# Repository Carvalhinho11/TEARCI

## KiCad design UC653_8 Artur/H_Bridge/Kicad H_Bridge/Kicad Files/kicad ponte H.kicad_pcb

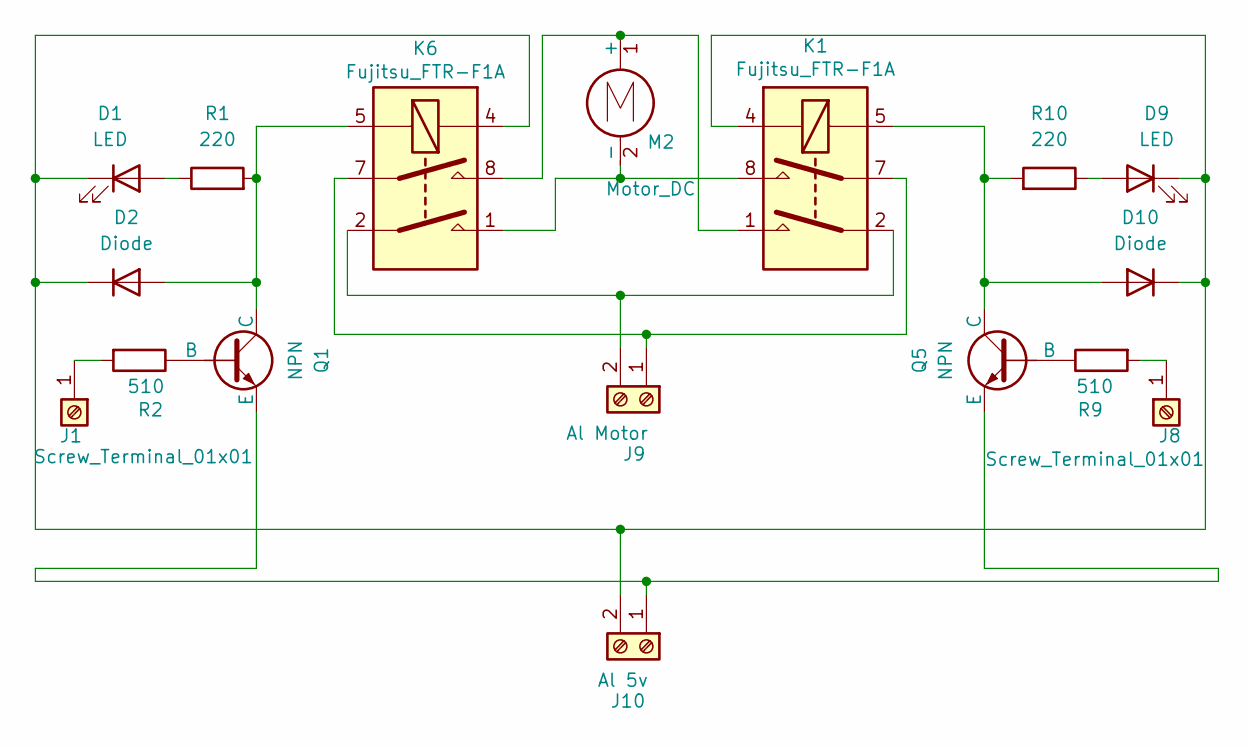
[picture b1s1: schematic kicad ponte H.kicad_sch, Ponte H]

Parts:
D1, D9: LED; LED_D3.0mm
D2, D10: Diode; D_SOD-523
J1, J8: Screw_Terminal_01x01; TerminalBlock_MetzConnect_360271_1x01_Horizontal_ScrewM3.0_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
J9: Al Motor; TerminalBlock_MetzConnect_Type101_RT01602HBWC_1x02_P5.08mm_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
J10: Al 5v; TerminalBlock_MetzConnect_Type101_RT01602HBWC_1x02_P5.08mm_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
K1, K6: Fujitsu_FTR-F1A; Relay_DPST_Fujitsu_FTR-F1A
M2: Motor_DC; TerminalBlock_MetzConnect_Type011_RT05502HBLC_1x02_P5.00mm_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
Q1, Q5: NPN; TO-92
R1, R10: 220; R_Axial_DIN0207_L6.3mm_D2.5mm_P7.62mm_Horizontal
R2, R9: 510; R_Axial_DIN0207_L6.3mm_D2.5mm_P7.62mm_Horizontal

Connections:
unnamed: D1.2 (A), R1.1
unnamed: D1.1 (K), D2.1 (K), D9.1 (K), D10.1 (K), J10.2, K1.4, K6.4
unnamed: D2.2 (A), K6.5, Q1.1 (C), R1.2
unnamed: D9.2 (A), R10.1
unnamed: D10.2 (A), K1.5, Q5.1 (C), R10.2
unnamed: J1.1, R2.2
unnamed: J8.1, R9.2
unnamed: J9.1, K1.7, K6.7
unnamed: J9.2, K1.2, K6.2
unnamed: J10.1, Q1.3 (E), Q5.3 (E)
unnamed: K1.1, K6.8, M2.1 (+)
unnamed: K1.8, K6.1, M2.2 (-)
unnamed: Q1.2 (B), R2.1
unnamed: Q5.2 (B), R9.1

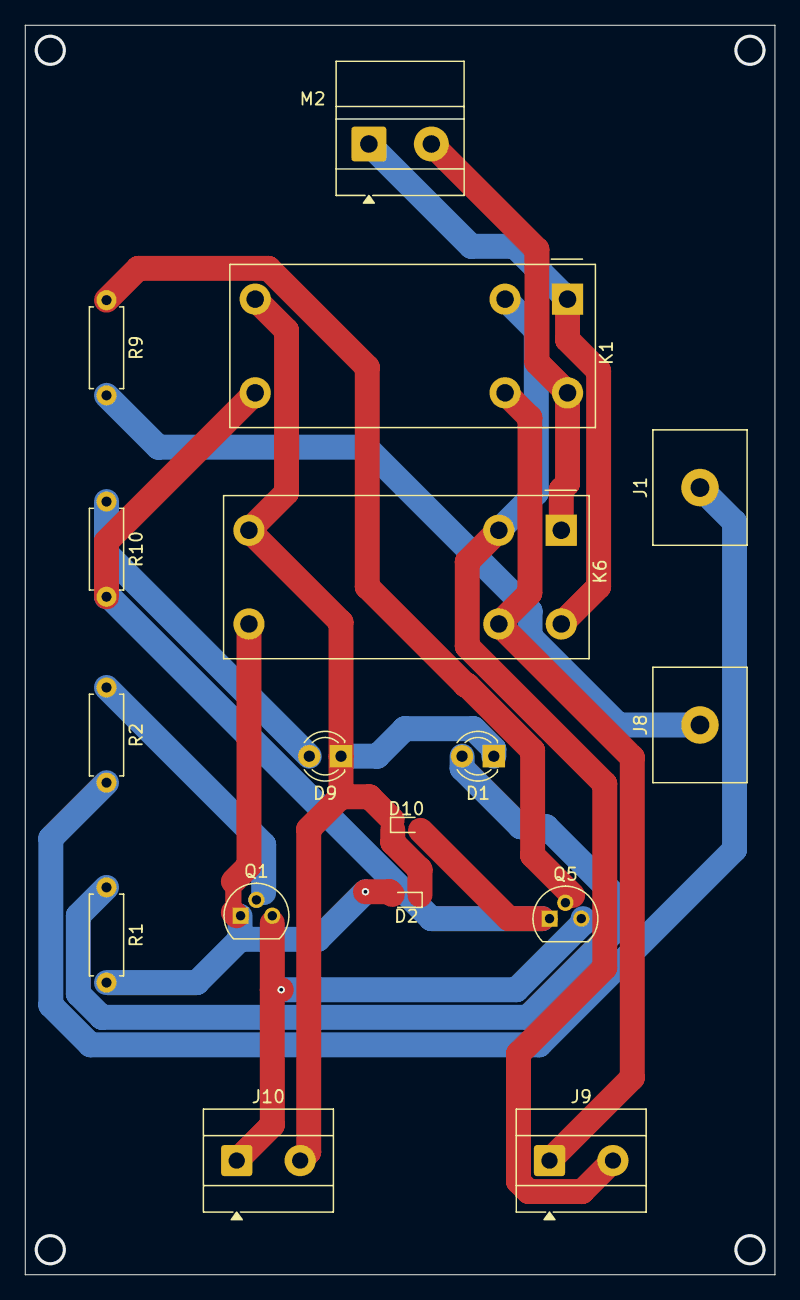
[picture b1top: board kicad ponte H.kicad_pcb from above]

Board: 2 copper layers, 60.0 x 100.0 mm, 17 parts (0 on the bottom side), 14 nets.

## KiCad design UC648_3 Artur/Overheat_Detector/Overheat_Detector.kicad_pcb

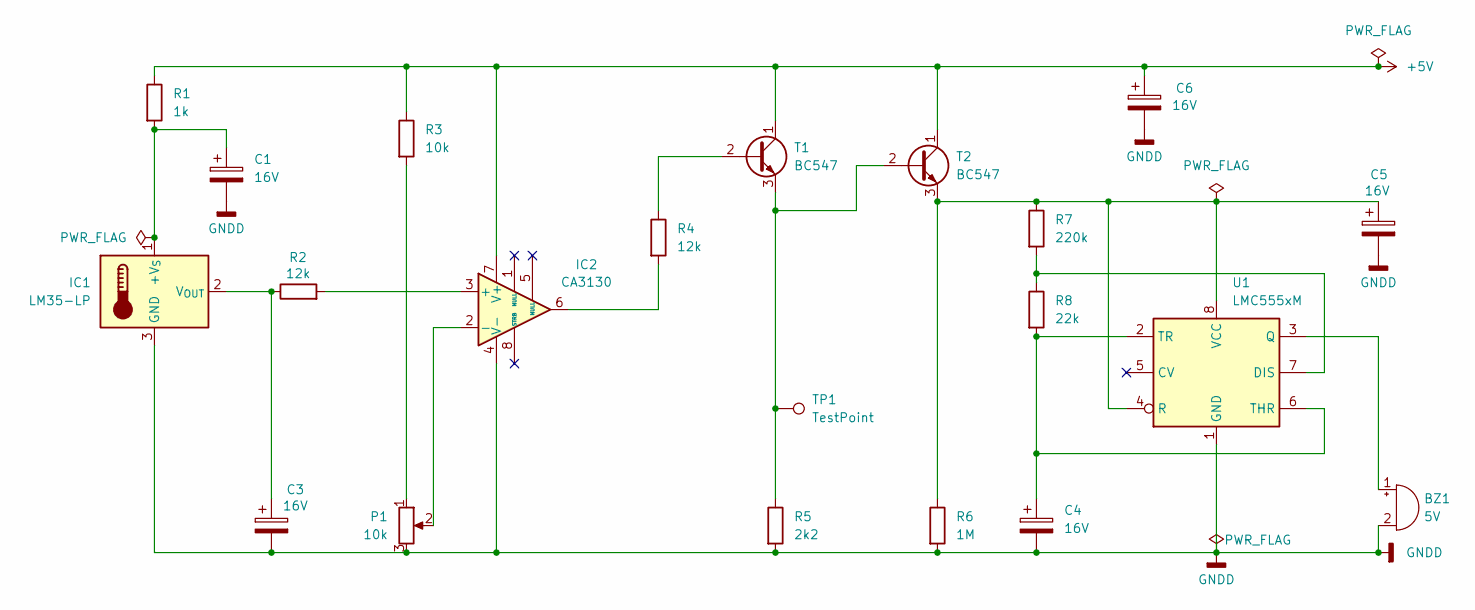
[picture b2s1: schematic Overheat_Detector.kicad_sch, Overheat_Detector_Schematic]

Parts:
BZ1: 5V; Buzzer_15x7.5RM7.6
C1, C3, C4, C5, C6: 16V; CP_Radial_D5.0mm_P2.00mm
IC1: LM35-LP; TO-92_Inline
IC2: CA3130; DIP-8_W7.62mm_LongPads
P1: 10k; Potentiometer_Bourns_3299W_Vertical
R1: 1k; R_Axial_DIN0204_L3.6mm_D1.6mm_P5.08mm_Horizontal
R2, R4: 12k; R_Axial_DIN0204_L3.6mm_D1.6mm_P5.08mm_Horizontal
R3: 10k; R_Axial_DIN0204_L3.6mm_D1.6mm_P5.08mm_Horizontal
R5: 2k2; R_Axial_DIN0204_L3.6mm_D1.6mm_P5.08mm_Horizontal
R6: 1M; R_Axial_DIN0204_L3.6mm_D1.6mm_P5.08mm_Horizontal
R7: 220k; R_Axial_DIN0204_L3.6mm_D1.6mm_P5.08mm_Horizontal
R8: 22k; R_Axial_DIN0204_L3.6mm_D1.6mm_P5.08mm_Horizontal
T1, T2: BC547; TO-92_Inline
TP1: TestPoint; TestPoint_THTPad_2.0x2.0mm_Drill1.0mm
U1: LMC555xM; SOIC-8_3.9x4.9mm_P1.27mm

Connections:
+5V: C6.1, IC2.7 (V+), R1.1, R3.1, T1.1 (C), T2.1 (C)
GNDD: BZ1.2 (-), C1.2, C3.2, C4.2, C5.2, C6.2, IC1.3 (GND), IC2.4 (V-), P1.3, R5.2, R6.2, U1.1 (GND)
unnamed: BZ1.1 (+), U1.3 (Q)
unnamed: C1.1, IC1.1 (+V_{S}), R1.2
unnamed: C3.1, IC1.2 (V_{OUT}), R2.1
unnamed: IC2.3 (+), R2.2
unnamed: IC2.2 (-), P1.2
unnamed: IC2.6, R4.2
unnamed: P1.1, R3.2
unnamed: R4.1, T1.2 (B)
unnamed: R5.1, T1.3 (E), T2.2 (B), TP1.1
unnamed: C5.1, R6.1, R7.1, T2.3 (E), U1.4 (R), U1.8 (VCC)
unnamed: R7.2, R8.1, U1.7 (DIS)
unnamed: C4.1, R8.2, U1.2 (TR), U1.6 (THR)

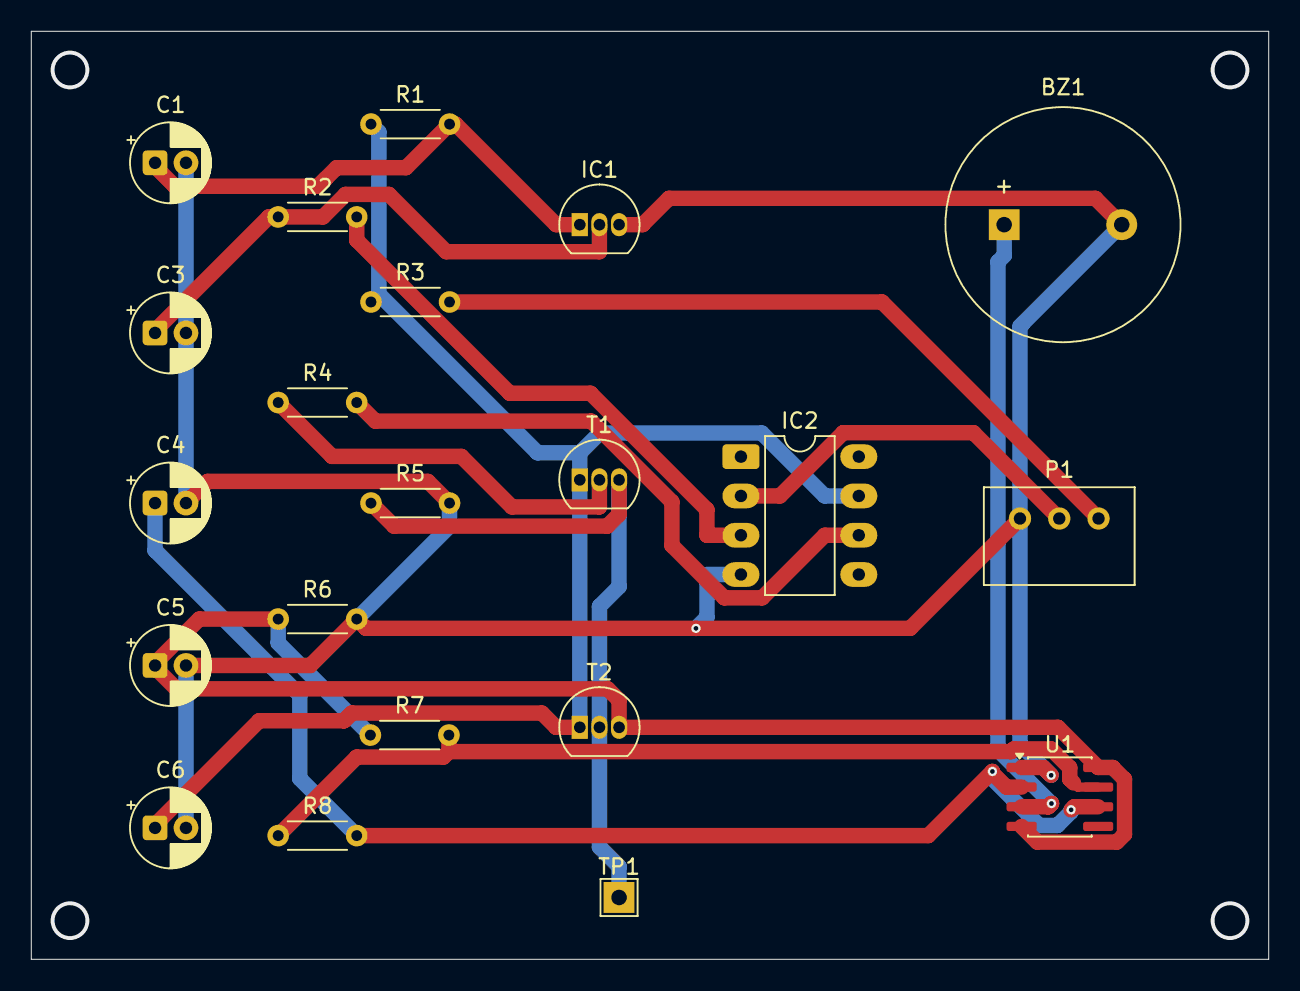
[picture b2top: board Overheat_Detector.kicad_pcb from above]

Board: 2 copper layers, 80.0 x 60.0 mm, 21 parts (0 on the bottom side), 14 nets.

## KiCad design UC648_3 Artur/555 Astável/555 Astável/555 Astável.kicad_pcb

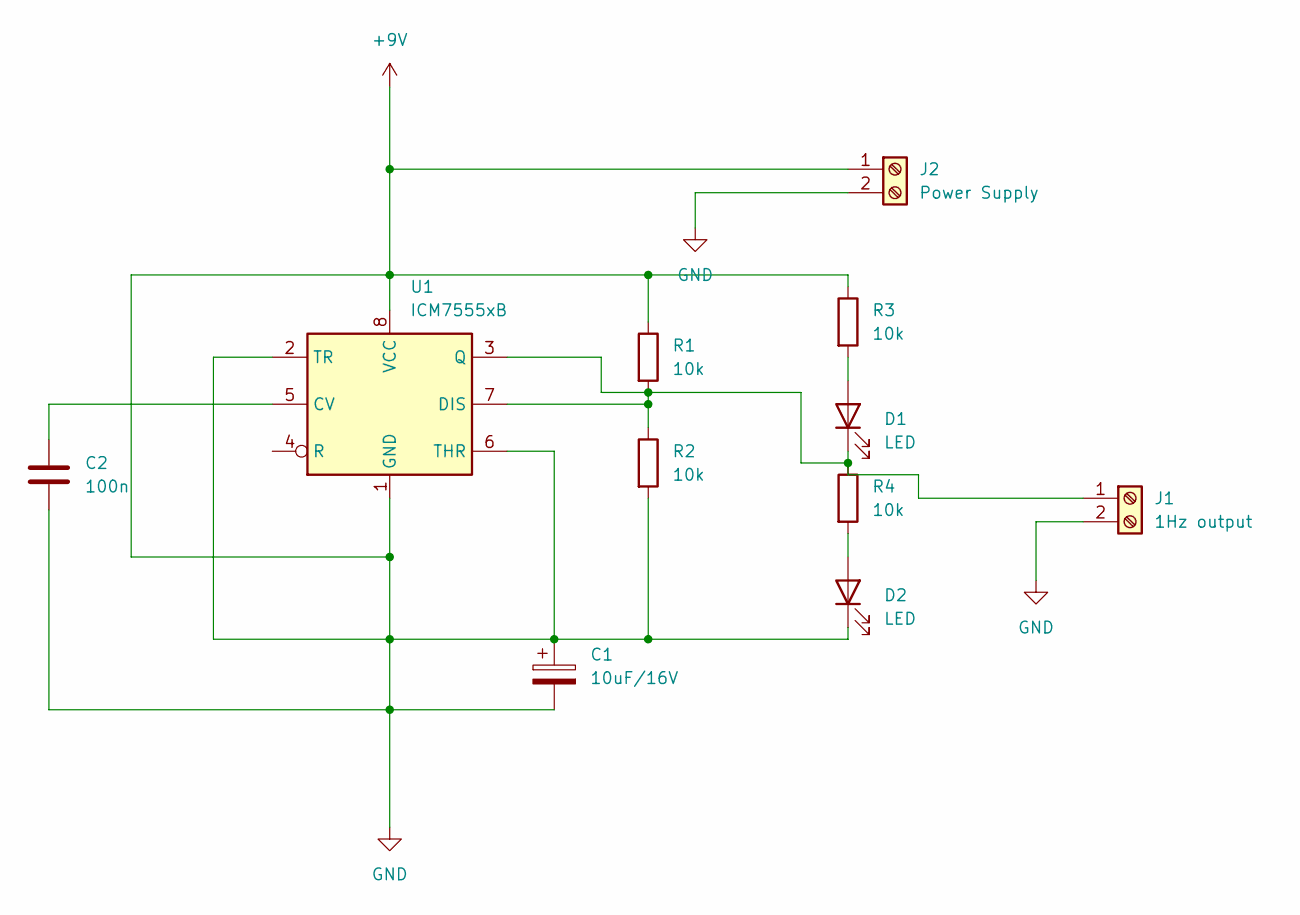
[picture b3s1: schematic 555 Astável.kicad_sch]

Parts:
C1: 10uF/16V; CP_Radial_D8.0mm_P5.00mm
C2: 100n; C_Rect_L18.0mm_W5.0mm_P15.00mm_FKS3_FKP3
D1, D2: LED; LED_D3.0mm
J1: 1Hz output; TerminalBlock_MaiXu_MX126-5.0-02P_1x02_P5.00mm
J2: Power Supply; TerminalBlock_MaiXu_MX126-5.0-02P_1x02_P5.00mm
R1, R2, R3, R4: 10k; R_Axial_DIN0204_L3.6mm_D1.6mm_P5.08mm_Horizontal
U1: ICM7555xB; DIP-8_W7.62mm

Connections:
+9V: C1.1, C1.2, C2.2, D2.1 (K), J1.2, J2.1, J2.2, R1.1, R2.2, R3.1, U1.1 (GND), U1.2 (TR), U1.6 (THR), U1.8 (VCC)
unnamed: D1.2 (A), R3.2
unnamed: D1.1 (K), J1.1, R1.2, R2.1, R4.1, U1.3 (Q), U1.7 (DIS)
unnamed: D2.2 (A), R4.2
unnamed: C2.1, U1.5 (CV)

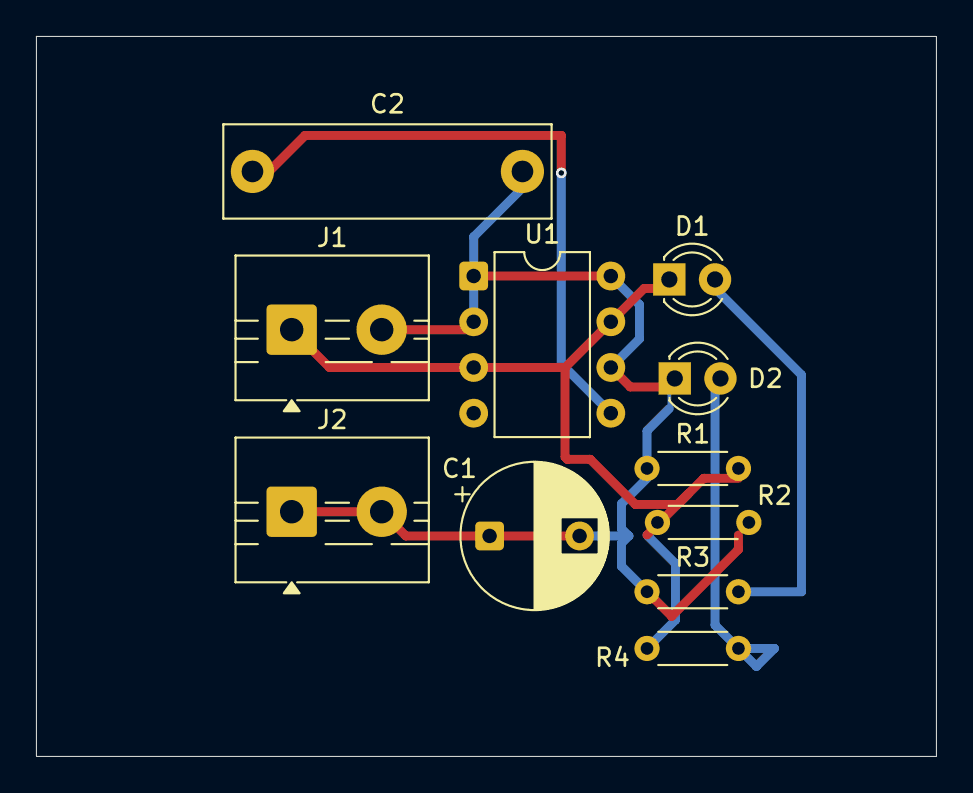
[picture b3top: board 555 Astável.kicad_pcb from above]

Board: 2 copper layers, 50.0 x 40.0 mm, 11 parts (0 on the bottom side), 5 nets.

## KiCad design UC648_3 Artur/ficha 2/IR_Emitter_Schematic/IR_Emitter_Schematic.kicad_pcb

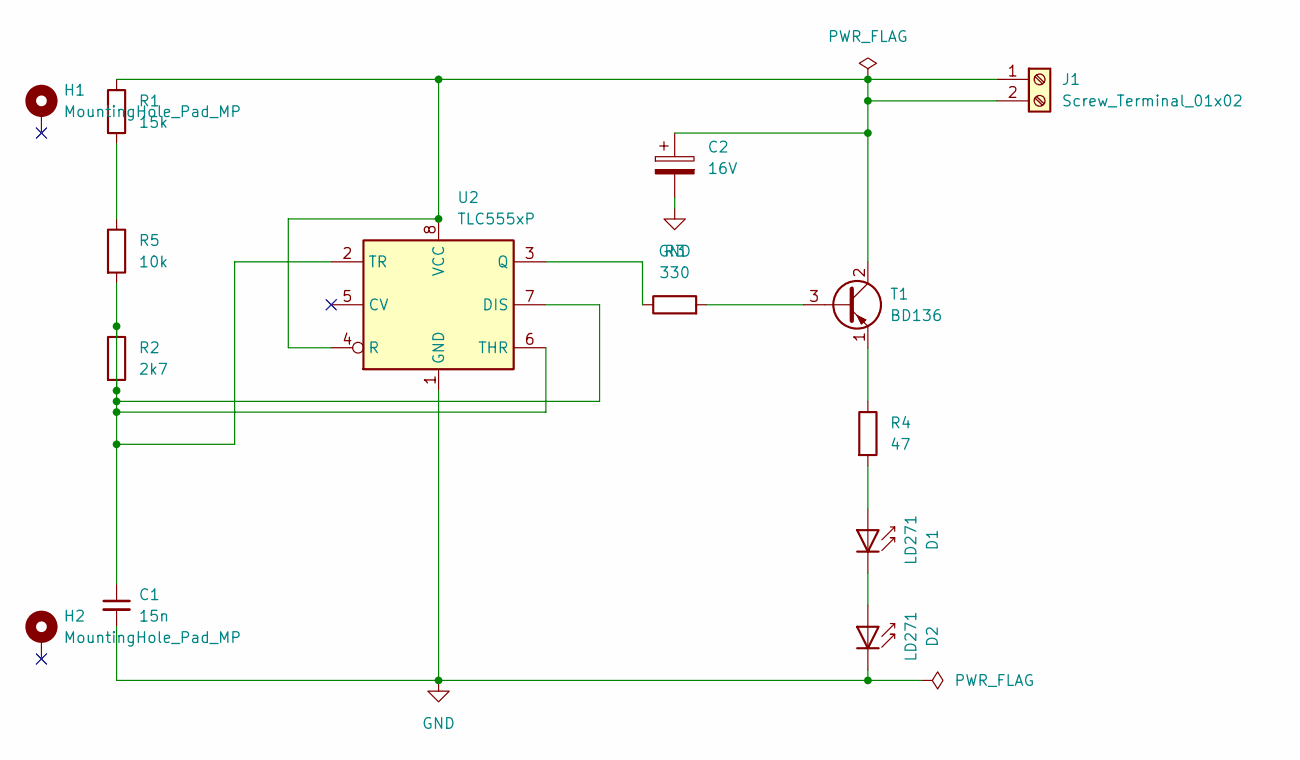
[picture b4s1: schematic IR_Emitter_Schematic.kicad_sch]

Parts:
C1: 15n; CP_Radial_D6.3mm_P2.50mm
C2: 16V; C_Disc_D3.0mm_W2.0mm_P2.50mm
D1, D2: LD271; LED_D5.0mm_IRGrey
H1, H2: MountingHole_Pad_MP; MountingHole_2.2mm_M2
J1: Screw_Terminal_01x02; TerminalBlock_MaiXu_MX126-5.0-02P_1x02_P5.00mm
R1: 15k; R_Axial_DIN0207_L6.3mm_D2.5mm_P7.62mm_Horizontal
R2: 2k7; R_Axial_DIN0207_L6.3mm_D2.5mm_P7.62mm_Horizontal
R3: 330; R_Axial_DIN0207_L6.3mm_D2.5mm_P7.62mm_Horizontal
R4: 47; R_Axial_DIN0207_L6.3mm_D2.5mm_P7.62mm_Horizontal
R5: 10k; R_Axial_DIN0207_L6.3mm_D2.5mm_P7.62mm_Horizontal
T1: BD136; TO-126-3_Vertical
U2: TLC555xP; DIP-8_W7.62mm

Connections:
GND: C1.2, C2.2, D2.1 (K), U2.1 (GND)
unnamed: D1.2 (A), R4.2
unnamed: D1.1 (K), D2.2 (A)
unnamed: C2.1, J1.1, J1.2, R1.1, T1.2 (C), U2.4 (R), U2.8 (VCC)
unnamed: R1.2, R5.1
unnamed: R3.2, T1.3 (B)
unnamed: R4.1, T1.1 (E)
unnamed: C1.1, R2.1, R2.2, R5.2, U2.2 (TR), U2.6 (THR), U2.7 (DIS)
unnamed: R3.1, U2.3 (Q)

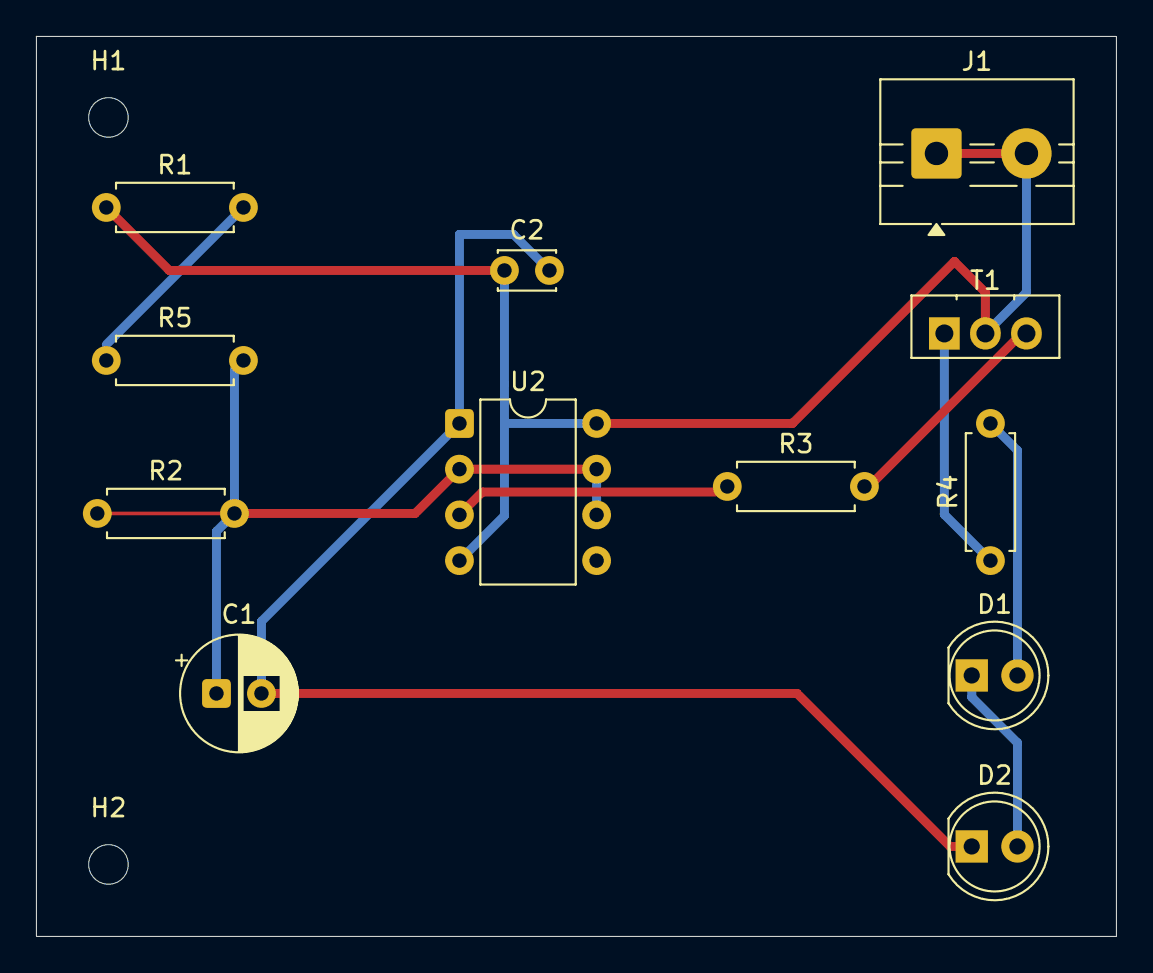
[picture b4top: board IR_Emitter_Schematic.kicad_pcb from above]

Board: 2 copper layers, 60.0 x 50.0 mm, 14 parts (0 on the bottom side), 9 nets.

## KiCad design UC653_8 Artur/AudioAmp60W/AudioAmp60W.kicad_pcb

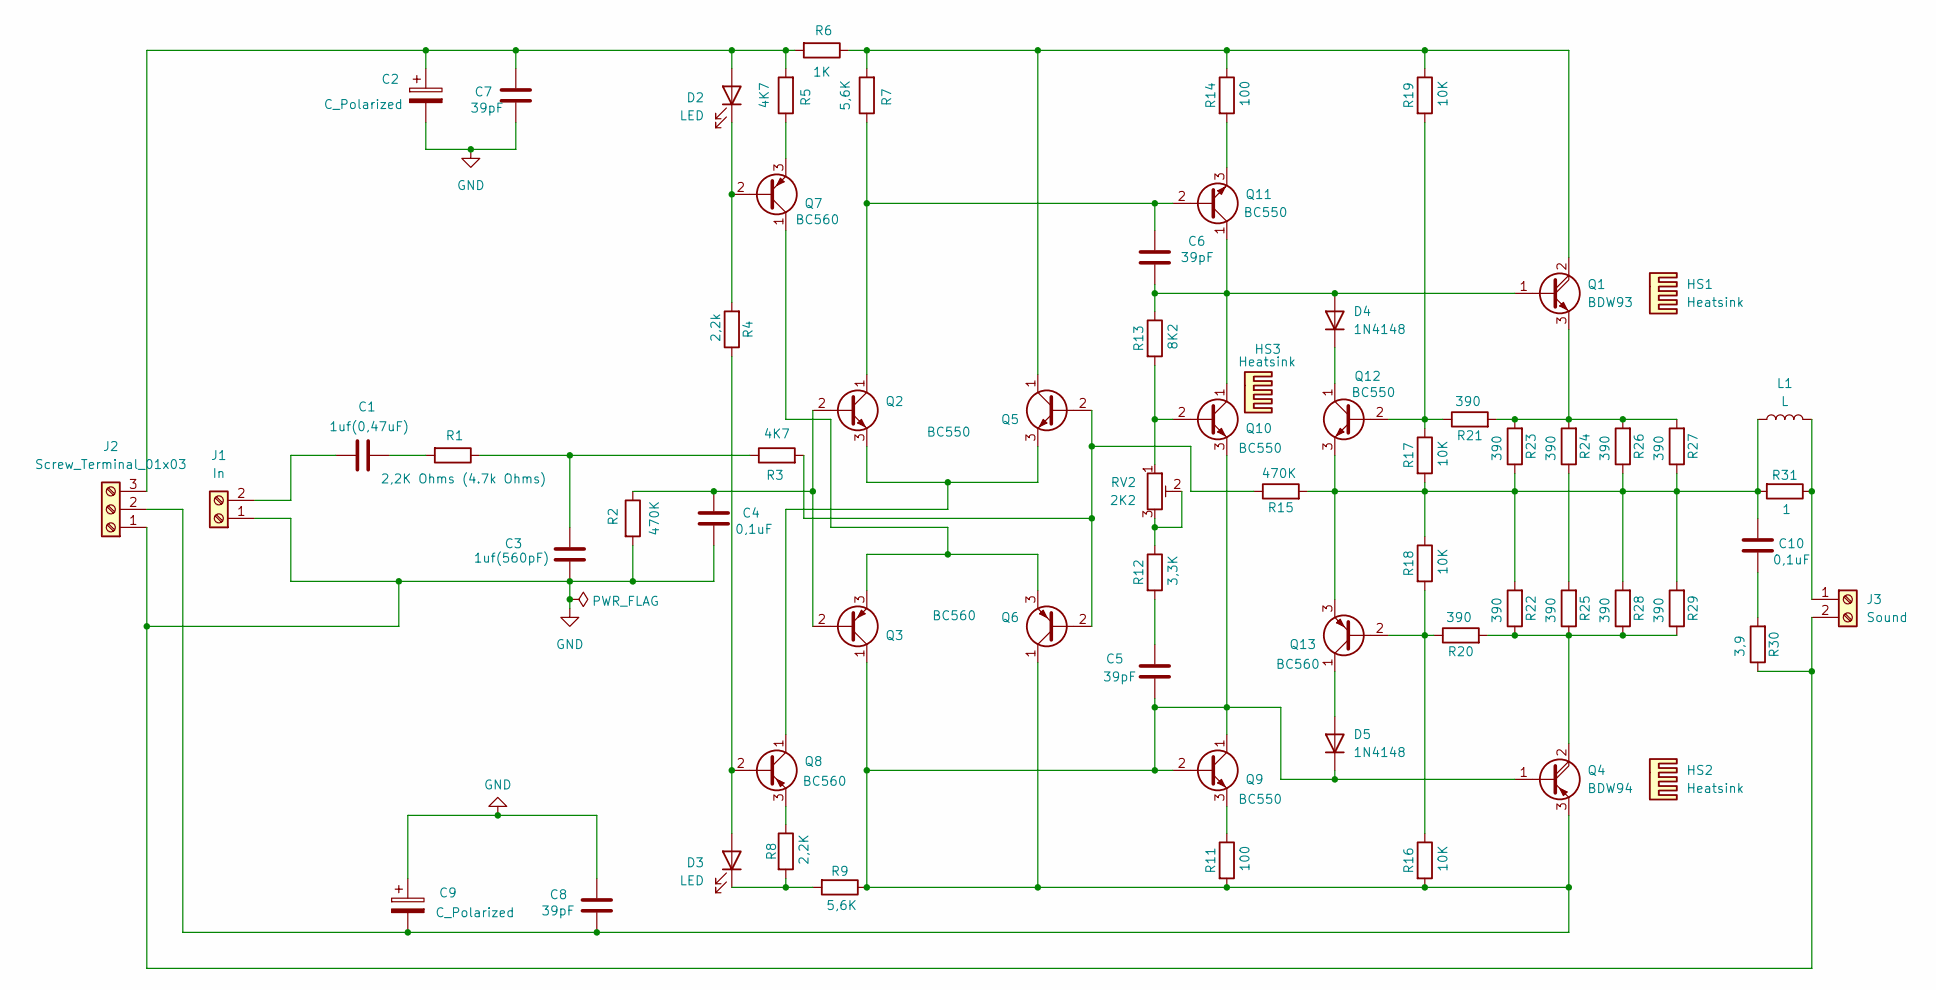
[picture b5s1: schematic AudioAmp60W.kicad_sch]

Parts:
C1: 1uf(0,47uF); C_Rect_L4.6mm_W2.0mm_P2.50mm_MKS02_FKP02
C2, C9: C_Polarized; CP_Radial_D4.0mm_P1.50mm
C3: 1uf(560pF); C_Rect_L4.6mm_W2.0mm_P2.50mm_MKS02_FKP02
C4, C10: 0,1uF; C_Rect_L4.6mm_W2.0mm_P2.50mm_MKS02_FKP02
C5, C6, C7, C8: 39pF; C_Rect_L4.6mm_W2.0mm_P2.50mm_MKS02_FKP02
D2, D3: LED; LED_Rectangular_W3.0mm_H2.0mm
D4, D5: 1N4148; D_DO-35_SOD27_P7.62mm_Horizontal
HS1, HS2, HS3: Heatsink
J1: In; TerminalBlock_Phoenix_MKDS-1-2-3.81_1x02_P3.81mm_Horizontal
J2: Screw_Terminal_01x03; TerminalBlock_Phoenix_MKDS-1,5-3_1x03_P5.00mm_Horizontal
J3: Sound; TerminalBlock_Phoenix_MKDS-1-2-3.81_1x02_P3.81mm_Horizontal
L1: L; L_Axial_L7.0mm_D3.3mm_P10.16mm_Horizontal_Fastron_MICC
Q1: BDW93; TO-220-3_Vertical
Q2, Q5, Q9, Q10, Q11, Q12: BC550; TO-92_Inline
Q3, Q6, Q7, Q8, Q13: BC560; TO-92_Inline
Q4: BDW94; TO-220-3_Vertical
R1: 2,2K Ohms (4.7k Ohms); R_Axial_DIN0204_L3.6mm_D1.6mm_P5.08mm_Horizontal
R2, R15: 470K; R_Axial_DIN0204_L3.6mm_D1.6mm_P5.08mm_Horizontal
R3, R5: 4K7; R_Axial_DIN0204_L3.6mm_D1.6mm_P5.08mm_Horizontal
R4: 2,2k; R_Axial_DIN0204_L3.6mm_D1.6mm_P5.08mm_Horizontal
R6: 1K; R_Axial_DIN0204_L3.6mm_D1.6mm_P5.08mm_Horizontal
R7, R9: 5,6K; R_Axial_DIN0204_L3.6mm_D1.6mm_P5.08mm_Horizontal
R8: 2,2K; R_Axial_DIN0204_L3.6mm_D1.6mm_P5.08mm_Horizontal
R11, R14: 100; R_Axial_DIN0204_L3.6mm_D1.6mm_P5.08mm_Horizontal
R12: 3,3K; R_Axial_DIN0204_L3.6mm_D1.6mm_P5.08mm_Horizontal
R13: 8K2; R_Axial_DIN0204_L3.6mm_D1.6mm_P5.08mm_Horizontal
R16, R17, R18, R19: 10K; R_Axial_DIN0204_L3.6mm_D1.6mm_P5.08mm_Horizontal
R20, R21, R22, R23, R24, R25, R26, R27, R28, R29: 390; R_Axial_DIN0204_L3.6mm_D1.6mm_P5.08mm_Horizontal
R30: 3,9; R_Axial_DIN0204_L3.6mm_D1.6mm_P5.08mm_Horizontal
R31: 1; R_Axial_DIN0204_L3.6mm_D1.6mm_P5.08mm_Horizontal
RV2: 2K2; Potentiometer_Bourns_3266W_Vertical

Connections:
GND: C2.2, C3.2, C4.2, C7.2, C8.1, C9.1, J1.1, J2.1, J3.2, R2.2, R30.1
unnamed: C1.1, R1.2
unnamed: C3.1, R1.1, R3.1
unnamed: C5.1, R12.2
unnamed: C10.1, R30.2
unnamed: C2.1, C7.1, D2.2 (A), J2.3, R5.2, R6.2
unnamed: D2.1 (K), Q7.2 (B), R4.2
unnamed: D3.2 (A), Q8.2 (B), R4.1
unnamed: D3.1 (K), R8.2, R9.2
unnamed: C6.1, D4.2 (A), Q1.1 (B), Q10.1 (C), Q11.1 (C), R13.1
unnamed: D4.1 (K), Q12.1 (C)
unnamed: D5.2 (A), Q13.1 (C)
unnamed: C5.2, C8.2, C9.2, D5.1 (K), J2.2, Q3.1 (C), Q4.1 (B), Q4.3 (E), Q6.1 (C), Q9.1 (C), Q9.2 (B), Q10.3 (E), R9.1, R11.2, R16.2
unnamed: C1.2, J1.2
unnamed: J3.1, L1.2, R31.1
unnamed: Q1.2 (C), Q5.1 (C), R6.1, R7.2, R14.1, R19.1
unnamed: Q1.3 (E), R21.2, R23.2, R24.2, R26.2, R27.2
unnamed: C4.1, Q2.2 (B), Q3.2 (B), R2.1
unnamed: Q2.3 (E), Q5.3 (E), Q8.1 (C)
unnamed: Q3.3 (E), Q6.3 (E), Q7.1 (C)
unnamed: Q4.2 (C), R20.2, R22.1, R25.1, R28.1, R29.1
unnamed: Q5.2 (B), Q6.2 (B), R3.2, R15.1
unnamed: Q7.3 (E), R5.1
unnamed: Q8.3 (E), R8.1
unnamed: Q9.3 (E), R11.1
unnamed: Q10.2 (B), R13.2, RV2.1
unnamed: C6.2, Q2.1 (C), Q11.2 (B), R7.1
unnamed: Q11.3 (E), R14.2
unnamed: Q12.2 (B), R17.1, R19.2, R21.1
unnamed: C10.2, L1.1, Q12.3 (E), Q13.3 (E), R15.2, R17.2, R18.1, R22.2, R23.1, R26.1, R27.1, R28.2, R29.2, R31.2
unnamed: Q13.2 (B), R16.1, R18.2, R20.1
unnamed: R12.1, RV2.2, RV2.3
unnamed: R24.1, R25.2

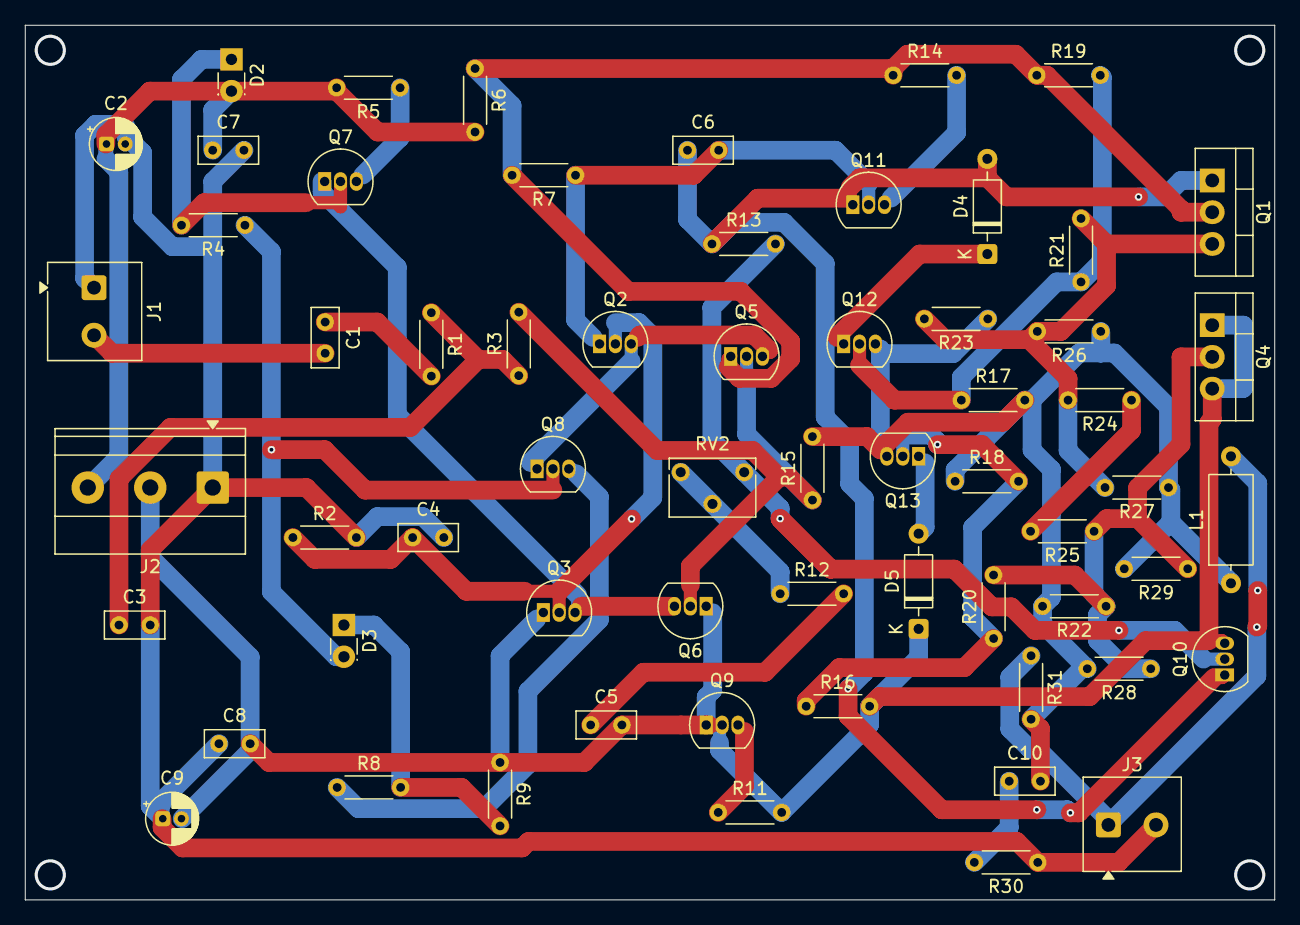
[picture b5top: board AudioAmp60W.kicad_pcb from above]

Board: 2 copper layers, 100.0 x 70.0 mm, 62 parts (0 on the bottom side), 33 nets.

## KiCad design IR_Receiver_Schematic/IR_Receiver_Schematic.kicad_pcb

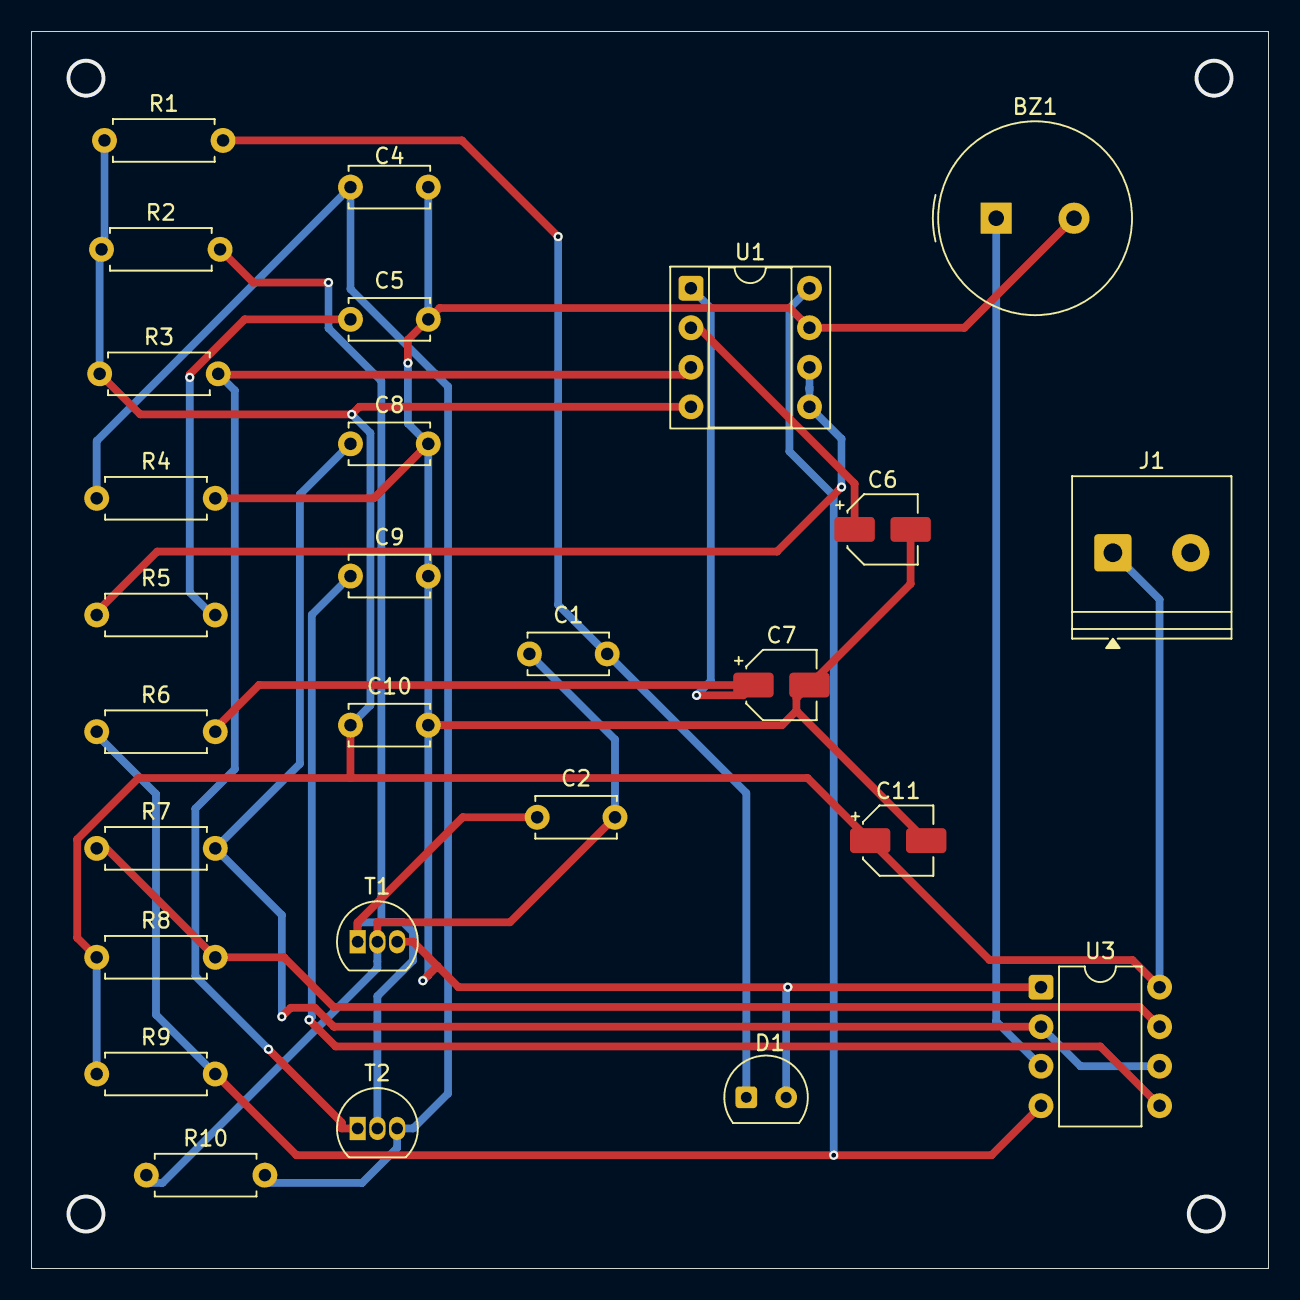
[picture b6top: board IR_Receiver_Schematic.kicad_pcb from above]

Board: 2 copper layers, 79.5 x 79.5 mm, 27 parts (0 on the bottom side), 16 nets.

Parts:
BZ1: Buzzer; Buzzer_TDK_PS1240P02BT_D12.2mm_H6.5mm
C1: 10n; C_Disc_D5.0mm_W2.5mm_P5.00mm
C2: 47p; C_Disc_D5.0mm_W2.5mm_P5.00mm
C4: 220n; C_Disc_D5.0mm_W2.5mm_P5.00mm
C5: 22n; C_Disc_D5.0mm_W2.5mm_P5.00mm
C6, C7, C11: 10V; CP_Elec_4x3
C8: 47n; C_Disc_D5.0mm_W2.5mm_P5.00mm
C9, C10: 100n; C_Disc_D5.0mm_W2.5mm_P5.00mm
D1: SFH205F; Osram_SFH205
J1: Screw_Terminal_01x01; TerminalBlock_Philmore_TB132_1x02_P5.00mm_Horizontal
R1: 6k8; R_Axial_DIN0207_L6.3mm_D2.5mm_P7.62mm_Horizontal
R2: 3k3; R_Axial_DIN0207_L6.3mm_D2.5mm_P7.62mm_Horizontal
R3: 2k2; R_Axial_DIN0207_L6.3mm_D2.5mm_P7.62mm_Horizontal
R4: 1k8; R_Axial_DIN0207_L6.3mm_D2.5mm_P7.62mm_Horizontal
R5: 10k; R_Axial_DIN0207_L6.3mm_D2.5mm_P7.62mm_Horizontal
R6: 1M; R_Axial_DIN0207_L6.3mm_D2.5mm_P7.62mm_Horizontal
R7: 100k; R_Axial_DIN0207_L6.3mm_D2.5mm_P7.62mm_Horizontal
R8: 1k; R_Axial_DIN0207_L6.3mm_D2.5mm_P7.62mm_Horizontal
R9: 4k7; R_Axial_DIN0207_L6.3mm_D2.5mm_P7.62mm_Horizontal
R10: 470k; R_Axial_DIN0207_L6.3mm_D2.5mm_P7.62mm_Horizontal
T1, T2: BC549; TO-92_Inline
U1: NE567; DIP-8_W7.62mm_Socket
U3: NE555P; DIP-8_W7.62mm

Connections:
+5V: C10.1, C11.1, J1.1, R1.1, R2.1, R3.1, R8.1, R9.1, U1.4 (VCC), U3.8 (VCC)
GNDD: BZ1.2 (-), C4.2, C5.2, C6.2, C7.2, C8.2, C9.2, C10.2, C11.2, D1.2 (A), R4.2, T1.3 (E), U1.7 (GND), U3.1 (GND)
unnamed: BZ1.1 (+), U3.3 (Q)
unnamed: C5.1, R5.2
unnamed: C1.2, D1.1 (K), R1.2
unnamed: C1.1, C2.2, R10.1, T1.2 (B)
unnamed: C2.1, R2.2, T1.1 (C), T2.2 (B)
unnamed: R3.2, T2.1 (C), U1.3 (INPUT)
unnamed: C4.1, R4.1, R10.2, T2.3 (E)
unnamed: C6.1, U1.2 (LP_FLT_C)
unnamed: C7.1, R6.2, U1.1 (OFLT_C)
unnamed: R6.1, R9.2, U1.8 (OUTPUT), U3.4 (R)
unnamed: R5.1, U1.5 (TIM_R), U1.6 (TIM_RC)
unnamed: C9.1, U3.5 (CV)
unnamed: R7.1, R8.2, U3.7 (DIS)
unnamed: C8.1, R7.2, U3.2 (TR), U3.6 (THR)
